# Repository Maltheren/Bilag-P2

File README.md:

# Bilag til P2 projektet ESD210
Alle eksterne bilag til P2 projektet for ESD210 hvor der kan findes følgende mapper:

### Kicad filer
Alle kredsløbsdiagrammer samt PCB designs. Under mappen /PDF kan alle schematics findes i pdf format.

### Kode produkt
De endelige 3 sketches for produktet. Det anbefales at åbne dem via platformIO.
Ellers kan den primære funktionskode findes i /src/main.cpp, samt de udviklede libraries under /lib.
Eksternt brugte libraries i dette projekt er:
- "Arduino.h"
- "RF24.h"

### Tests
Her forefindes de forskellige tests opdelt som enten samlet, Klokke eller MKF

### PC oscilloskop
For at visualisere de samples der tages af arduinoen på MKF-modulet benyttes følgende værktøj
https://x-io.co.uk/serial-oscilloscope/

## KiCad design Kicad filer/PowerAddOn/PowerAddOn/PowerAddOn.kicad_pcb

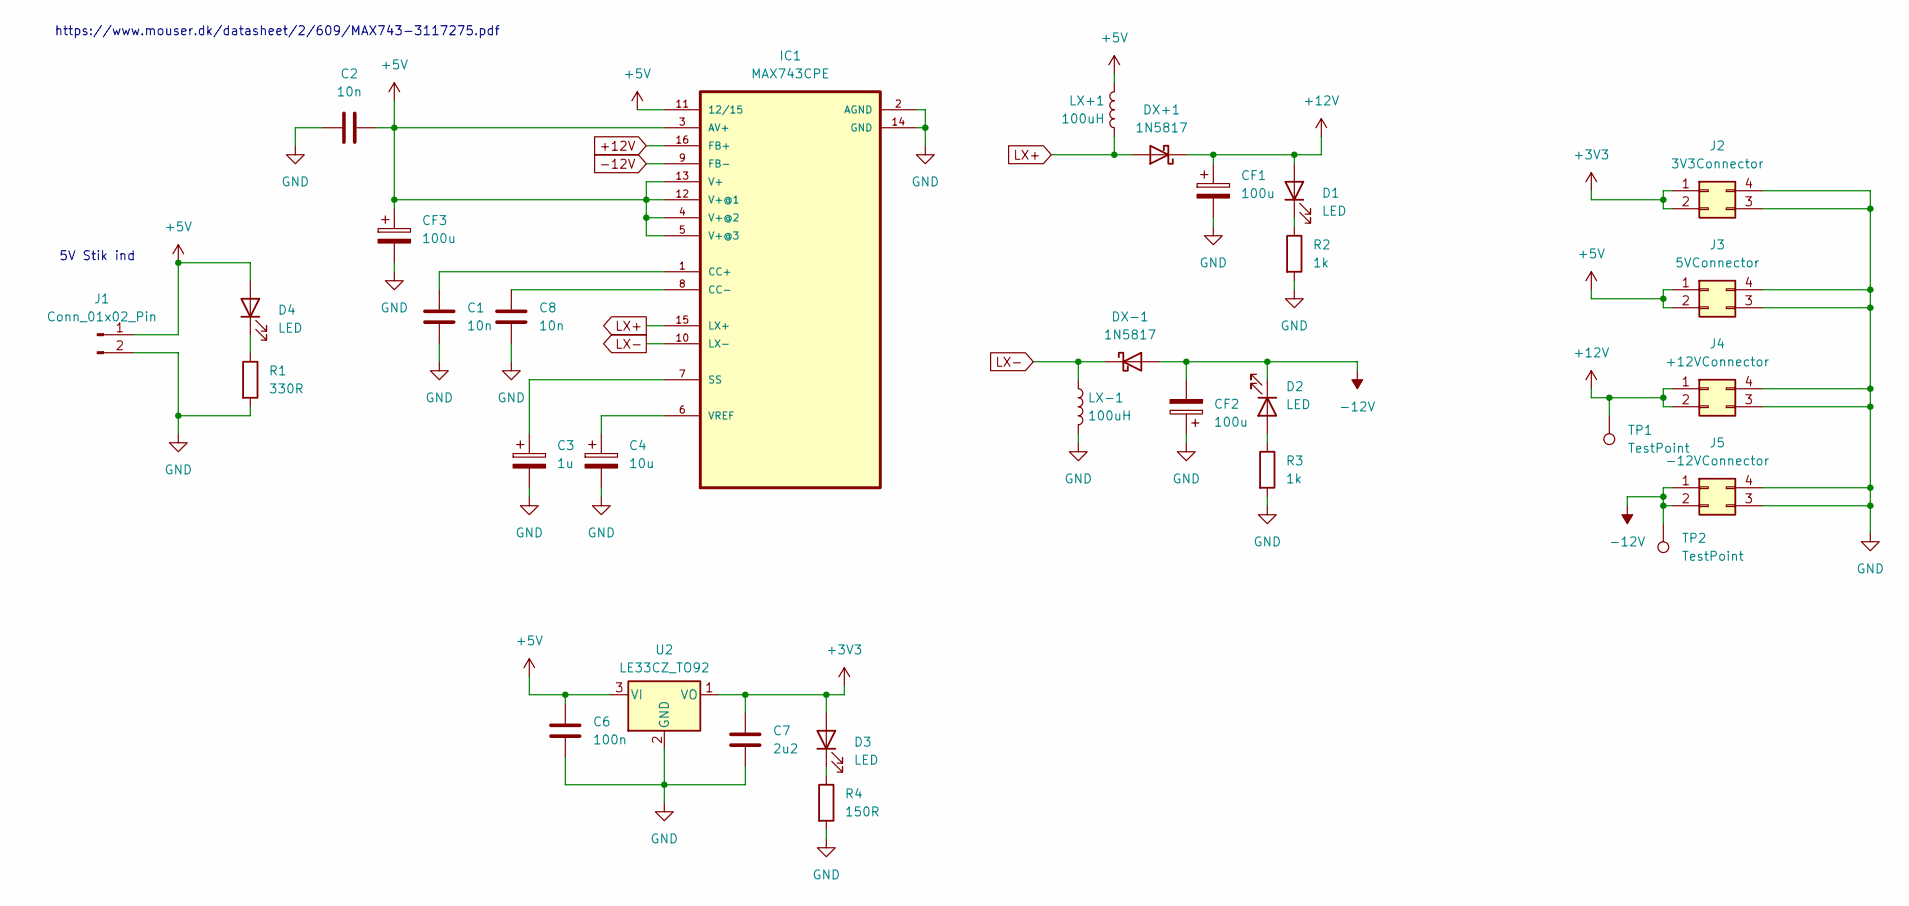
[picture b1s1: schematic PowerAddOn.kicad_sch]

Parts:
C1, C2, C8: 10n; C_Disc_D4.7mm_W2.5mm_P5.00mm
C3: 1u; CP_Radial_D4.0mm_P2.00mm
C4: 10u; CP_Radial_D4.0mm_P2.00mm
C6: 100n; C_0805_2012Metric_Pad1.18x1.45mm_HandSolder
C7: 2u2; C_0805_2012Metric_Pad1.18x1.45mm_HandSolder
CF1, CF2, CF3: 100u; CP_Axial_L10.0mm_D6.0mm_P15.00mm_Horizontal
D1, D2, D3, D4: LED; LED_D3.0mm
DX+1: 1N5817; D_DO-41_SOD81_P10.16mm_Horizontal
DX-1: 1N5817; D_DO-41_SOD81_P10.16mm_Horizontal
IC1: MAX743CPE; DIP794W47P254L1943H457Q16
J1: Conn_01x02_Pin; PinHeader_1x02_P2.54mm_Vertical
J2: 3V3Connector; PinHeader_2x02_P2.54mm_Vertical
J3: 5VConnector; PinHeader_2x02_P2.54mm_Vertical
J4: +12VConnector; PinHeader_2x02_P2.54mm_Vertical
J5: -12VConnector; PinHeader_2x02_P2.54mm_Vertical
LX+1: 100uH; L_Radial_D10.0mm_P5.00mm_Fastron_07P
LX-1: 100uH; L_Radial_D10.0mm_P5.00mm_Fastron_07P
R1: 330R; R_0805_2012Metric_Pad1.20x1.40mm_HandSolder
R2, R3: 1k; R_0805_2012Metric_Pad1.20x1.40mm_HandSolder
R4: 150R; R_0805_2012Metric_Pad1.20x1.40mm_HandSolder
TP1, TP2: TestPoint; TestPoint_Pad_4.0x4.0mm
U2: LE33CZ_TO92; TO-92_Inline

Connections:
+3V3: C7.1, D3.2 (A), J2.1, J2.2, U2.1 (VO)
+5V: C2.2, C6.1, CF3.1, D4.2 (A), IC1.3 (AV+), IC1.4 (V+@2), IC1.5 (V+@3), IC1.11 (12/15), IC1.12 (V+@1), IC1.13 (V+), J1.1, J3.1, J3.2, LX+1.1, U2.3 (VI)
+12V: CF1.1, D1.2 (A), DX+1.1 (K), IC1.16 (FB+), J4.1, J4.2, TP1.1
-12V: CF2.2, D2.1 (K), DX-1.2 (A), IC1.9 (FB-), J5.1, J5.2, TP2.1
GND: C1.2, C2.1, C3.2, C4.2, C6.2, C7.2, C8.2, CF1.2, CF2.1, CF3.2, IC1.2 (AGND), IC1.14 (GND), J1.2, J2.3, J2.4, J3.3, J3.4, J4.3, J4.4, J5.3, J5.4, LX-1.2, R1.2, R2.2, R3.2, R4.2, U2.2 (GND)
LX+: DX+1.2 (A), IC1.15 (LX+), LX+1.2
LX-: DX-1.1 (K), IC1.10 (LX-), LX-1.1
unnamed: D1.1 (K), R2.1
unnamed: D2.2 (A), R3.1
unnamed: D3.1 (K), R4.1
unnamed: D4.1 (K), R1.1
unnamed: C1.1, IC1.1 (CC+)
unnamed: C8.1, IC1.8 (CC-)
unnamed: C3.1, IC1.7 (SS)
unnamed: C4.1, IC1.6 (VREF)

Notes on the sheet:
5V Stik ind
https://www.mouser.dk/datasheet/2/609/MAX743-3117275.pdf

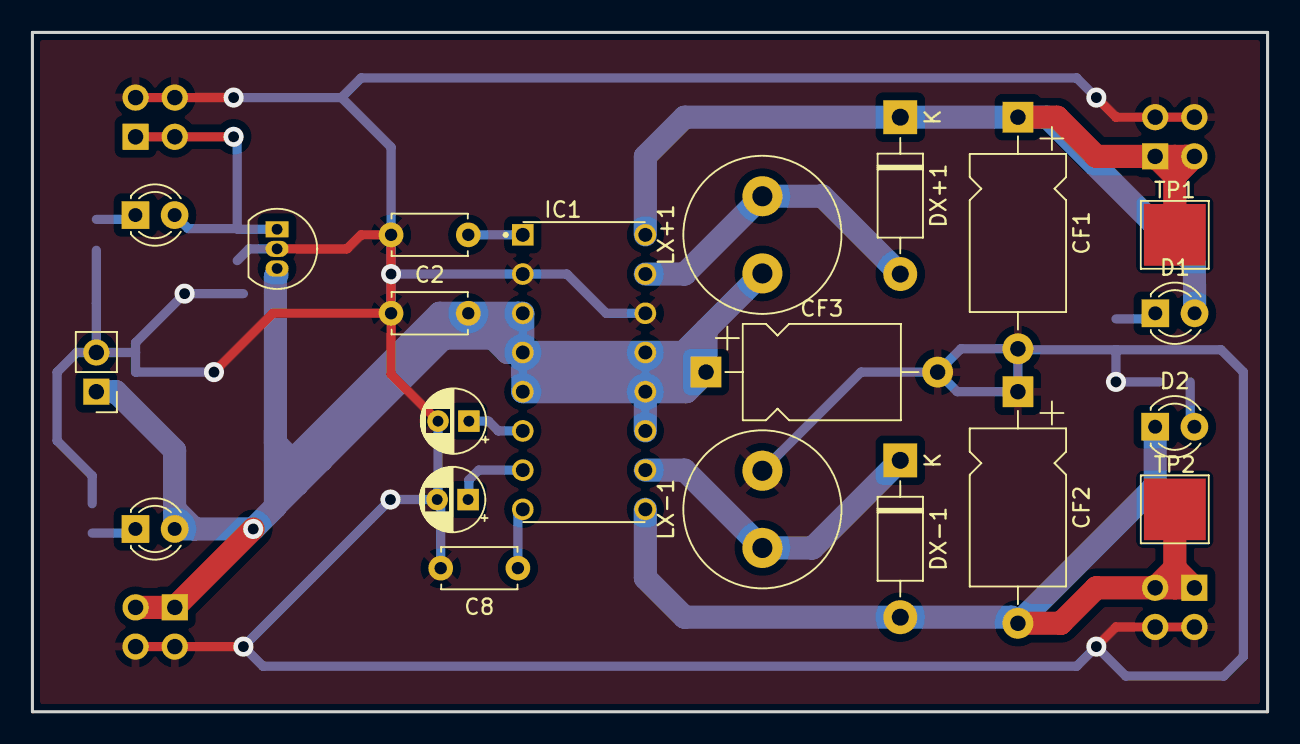
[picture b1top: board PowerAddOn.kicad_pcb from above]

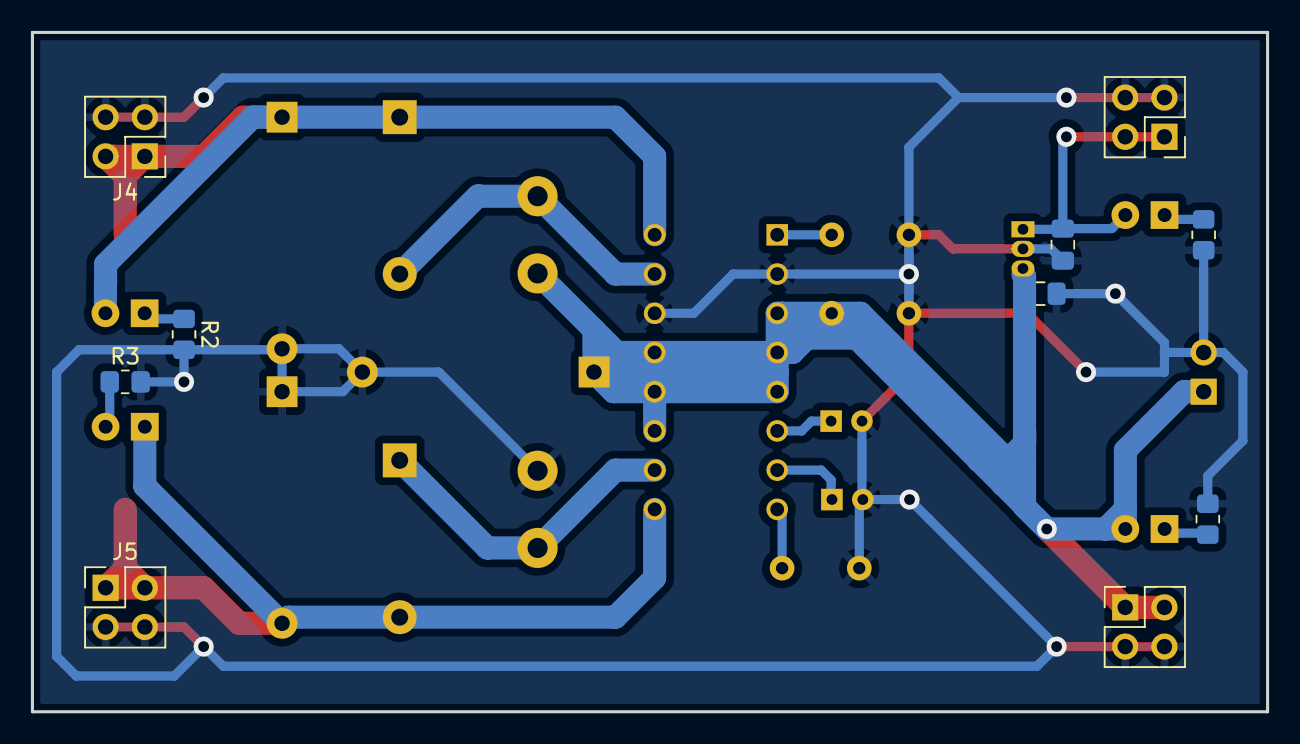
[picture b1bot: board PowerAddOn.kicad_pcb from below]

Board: 2 copper layers, 80.0 x 44.0 mm, 31 parts (10 on the bottom side), 15 nets.

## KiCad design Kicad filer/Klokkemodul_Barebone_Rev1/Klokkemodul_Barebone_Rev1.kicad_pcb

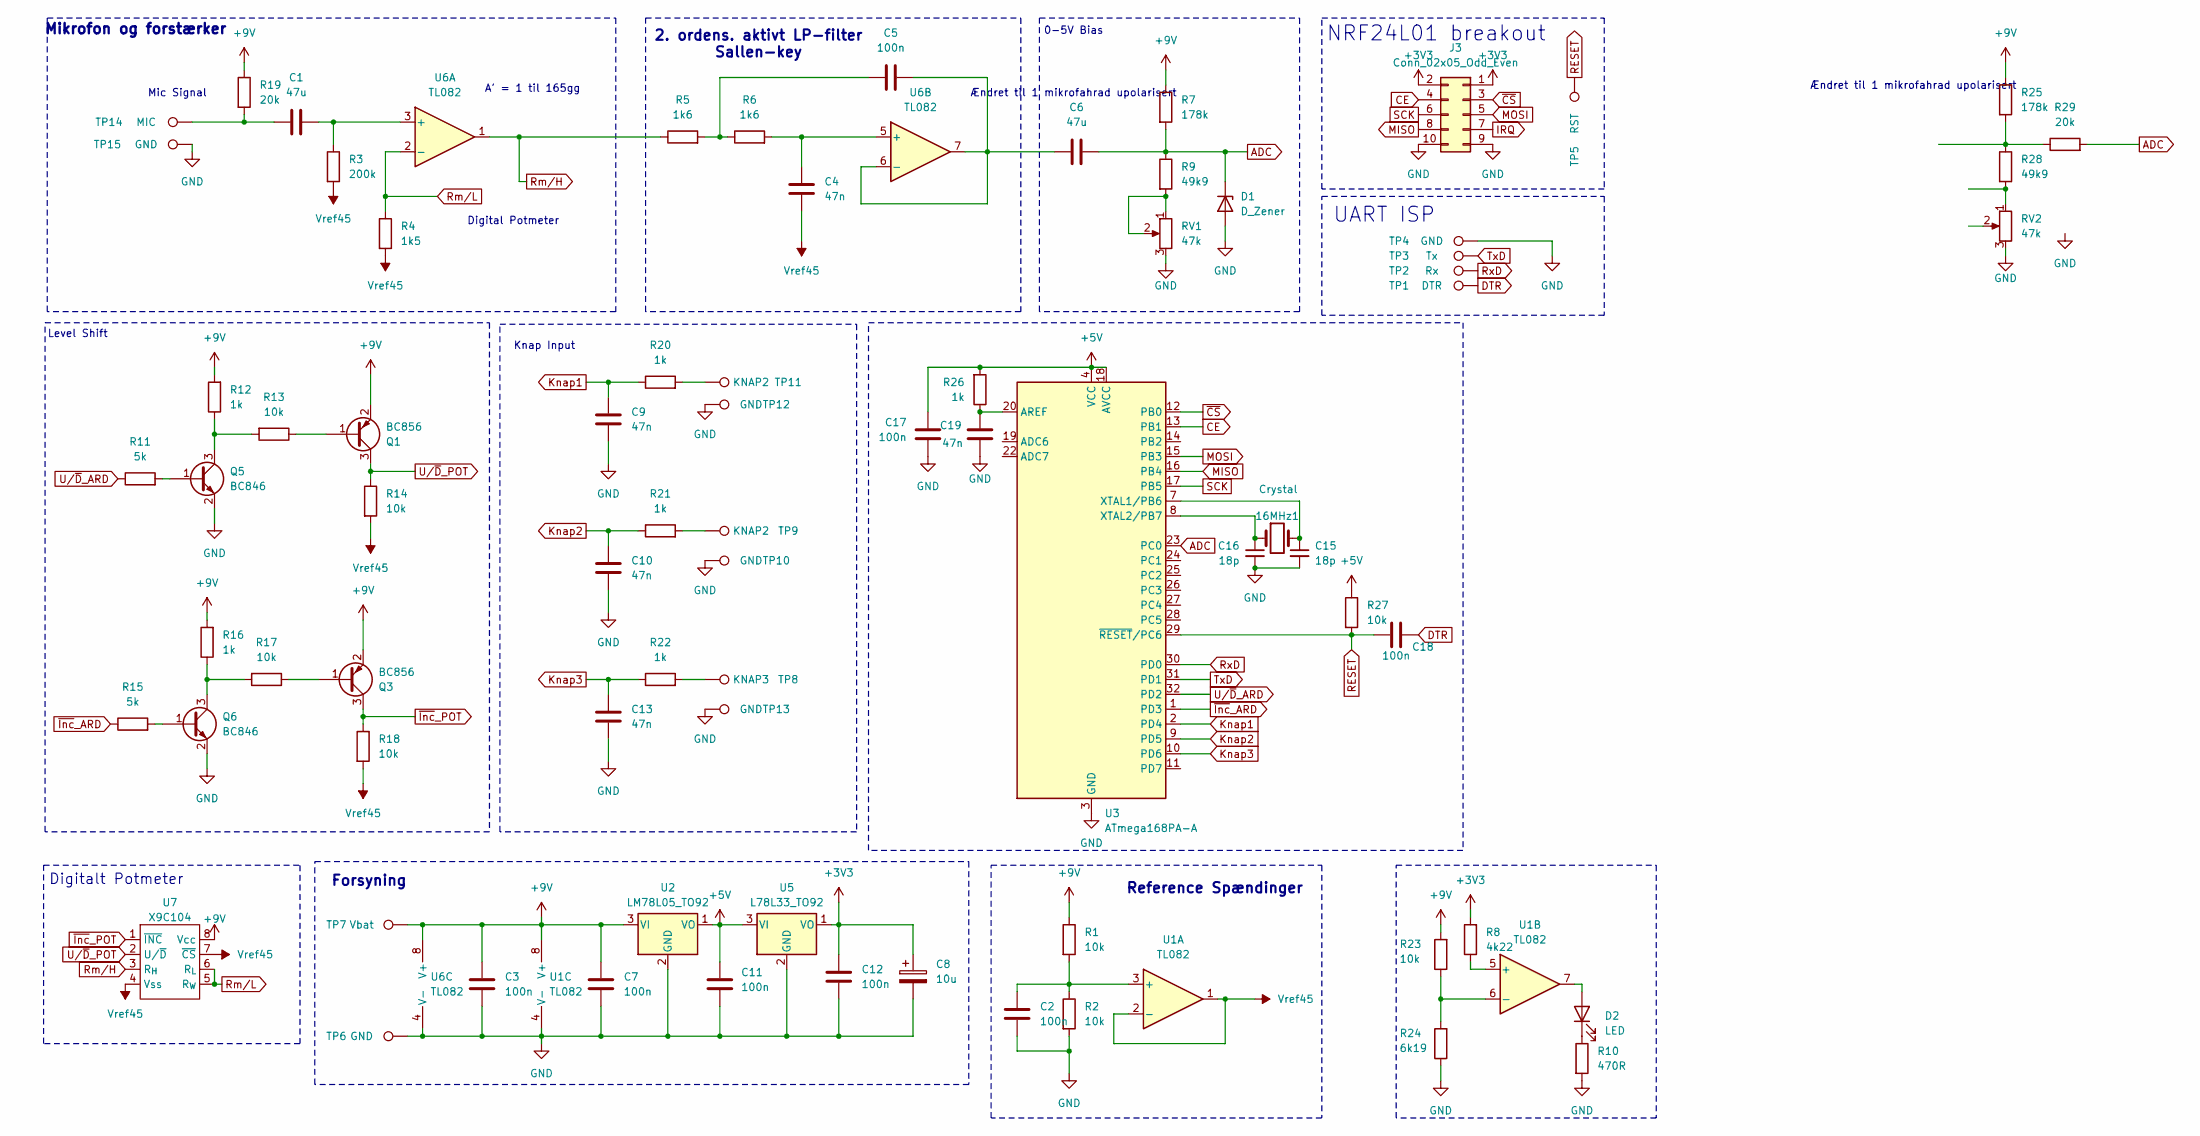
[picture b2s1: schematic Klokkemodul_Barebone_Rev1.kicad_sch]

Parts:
16MHz1: Crystal; Crystal_HC18-U_Vertical
C1, C6: 47u; CP_Radial_D5.0mm_P2.50mm
C2, C3, C5, C7, C11, C12, C17, C18: 100n; C_0603_1608Metric_Pad1.08x0.95mm_HandSolder
C4, C9, C10, C13, C19: 47n; C_0603_1608Metric_Pad1.08x0.95mm_HandSolder
C8: 10u; CP_Radial_D5.0mm_P2.50mm
C15, C16: 18p; C_0603_1608Metric_Pad1.08x0.95mm_HandSolder
D1: D_Zener; D_DO-15_P10.16mm_Horizontal
D2: LED; LED_D3.0mm
J3: Conn_02x05_Odd_Even; PinSocket_2x05_P2.54mm_Vertical
Q1, Q3: BC856; SOT-23
Q5, Q6: BC846; SOT-23
R1, R2, R13, R14, R17, R18, R23, R27: 10k; R_0603_1608Metric_Pad0.98x0.95mm_HandSolder
R3: 200k; R_0603_1608Metric_Pad0.98x0.95mm_HandSolder
R4: 1k5; R_0603_1608Metric_Pad0.98x0.95mm_HandSolder
R5, R6: 1k6; R_0603_1608Metric_Pad0.98x0.95mm_HandSolder
R7, R25: 178k; R_0603_1608Metric_Pad0.98x0.95mm_HandSolder
R8: 4k22; R_0603_1608Metric_Pad0.98x0.95mm_HandSolder
R9, R28: 49k9; R_0603_1608Metric_Pad0.98x0.95mm_HandSolder
R10: 470R; R_0603_1608Metric_Pad0.98x0.95mm_HandSolder
R11, R15: 5k; R_0603_1608Metric_Pad0.98x0.95mm_HandSolder
R12, R16, R20, R21, R22, R26: 1k; R_0603_1608Metric_Pad0.98x0.95mm_HandSolder
R19, R29: 20k; R_0603_1608Metric_Pad0.98x0.95mm_HandSolder
R24: 6k19; R_0603_1608Metric_Pad0.98x0.95mm_HandSolder
RV1, RV2: 47k; Potentiometer_ACP_CA9-V10_Vertical_Hole
TP1: DTR; TestPoint_Pad_2.5x2.5mm
TP2: Rx; TestPoint_Pad_2.5x2.5mm
TP3: Tx; TestPoint_Pad_2.5x2.5mm
TP4, TP6, TP10, TP12, TP13, TP15: GND; TestPoint_Pad_2.5x2.5mm
TP5: RST; TestPoint_Pad_2.5x2.5mm
TP7: Vbat; TestPoint_Pad_2.5x2.5mm
TP8: KNAP3; TestPoint_Pad_2.5x2.5mm
TP9, TP11: KNAP2; TestPoint_Pad_2.5x2.5mm
TP14: MIC; TestPoint_Pad_2.5x2.5mm
U1, U6: TL082; SOIC-8_3.9x4.9mm_P1.27mm
U2: LM78L05_TO92; TO-92_Inline
U3: ATmega168PA-A; TQFP-32_7x7mm_P0.8mm
U5: L78L33_TO92; TO-92_Inline
U7: X9C104; SOIC-8_3.9x4.9mm_P1.27mm

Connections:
+3V3: C8.1, C12.1, J3.1, J3.2, R8.2, U5.1 (VO)
+5V: C11.1, C17.1, R26.2, R27.1, U2.1 (VO), U3.4 (VCC), U3.6 (VCC), U3.18 (AVCC), U5.3 (VI)
+9V: C3.1, C7.1, Q1.2 (E), Q3.2 (E), R1.1, R7.1, R12.2, R16.2, R19.1, R23.2, R25.1, TP7.1, U1.8 (V+), U2.3 (VI), U6.8 (V+), U7.8 (Vcc); also elsewhere on the board
ADC: C6.2, D1.1 (K), R7.2, R9.1, R29.2, U3.23 (PC0)
CE: J3.4, U3.13 (PB1)
DTR: C18.1, TP1.1
GND: C2.2, C3.2, C7.2, C8.2, C9.2, C10.2, C11.2, C12.2, C13.2, C15.2, C16.2, C17.2, C19.2, D1.2 (A), J3.9, J3.10, Q5.2 (E), Q6.2 (E), R2.2, R10.2, R24.1, RV1.3, RV2.3, TP4.1, TP6.1, TP10.1, TP12.1, TP13.1, TP15.1, U1.4 (V-), U2.2 (GND), U3.3 (GND), U3.5 (GND), U3.21 (GND), U5.2 (GND), U6.4 (V-)
IRQ: J3.7
Knap1: C9.1, R20.1, U3.2 (PD4)
Knap2: C10.1, R21.1, U3.9 (PD5)
Knap3: C13.1, R22.1, U3.10 (PD6)
MISO: J3.8, U3.16 (PB4)
MOSI: J3.5, U3.15 (PB3)
unnamed: C1.1, R19.2, TP14.1
unnamed: C5.1, R5.2, R6.1
unnamed: D2.2 (A), U1.7
unnamed: D2.1 (K), R10.1
unnamed 17: Q1.1 (B), R13.1; also elsewhere on the board
unnamed 18: Q3.1 (B), R17.1; also elsewhere on the board
unnamed: Q5.1 (B), R11.2
unnamed: Q5.3 (C), R12.1, R13.2
unnamed: Q6.1 (B), R15.2
unnamed: Q6.3 (C), R16.1, R17.2
unnamed: R9.2, RV1.1, RV1.2
unnamed: R20.2, TP11.1
unnamed: R21.2, TP9.1
unnamed: R22.2, TP8.1
unnamed: R25.2, R28.1, R29.1
unnamed: R28.2, RV2.1
unnamed: C2.1, R1.2, R2.1, U1.3 (+)
unnamed: R8.1, U1.5 (+)
unnamed: R23.1, R24.2, U1.6 (-)
unnamed: C19.1, R26.1, U3.20 (AREF)
unnamed: 16MHz1.2, C15.1, U3.7 (XTAL1/PB6)
unnamed: 16MHz1.1, C16.1, U3.8 (XTAL2/PB7)
unnamed: C1.2, R3.1, U6.3 (+)
unnamed: C4.1, R6.2, U6.5 (+)
unnamed: C5.2, C6.1, U6.6 (-), U6.7
RESET: C18.2, R27.2, TP5.1, U3.29 (~RESET/PC6)
Rm/H: R5.1, U6.1, U7.3 (R_{H})
Rm/L: R4.1, U6.2 (-), U7.5 (R_{W}), U7.6 (R_{L})
RxD: TP2.1, U3.30 (PD0)
SCK: J3.6, U3.17 (PB5)
TxD: TP3.1, U3.31 (PD1)
U/~D_ARD: R11.1, U3.32 (PD2)
U/~D_POT: Q1.3 (C), R14.1, U7.2 (U/~D); also elsewhere on the board
Vref45: C4.2, R3.2, R4.2, R14.2, R18.2, U1.1, U1.2 (-), U7.4 (Vss), U7.7 (~CS)
~CS: J3.3, U3.12 (PB0)
~Inc_ARD: R15.1, U3.1 (PD3)
~Inc_POT: Q3.3 (C), R18.1, U7.1 (~INC); also elsewhere on the board

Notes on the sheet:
Digitalt Potmeter
Digital Potmeter
2. ordens. aktivt LP-filter Sallen-key
A' = 1 til 165gg
0-5V Bias
Ændret til 1 mikrofahrad upolarisert
NRF24L01 breakout
Mic Signal
Knap Input
Forsyning
UART ISP
Level Shift
Reference Spændinger
Mikrofon og forstærker

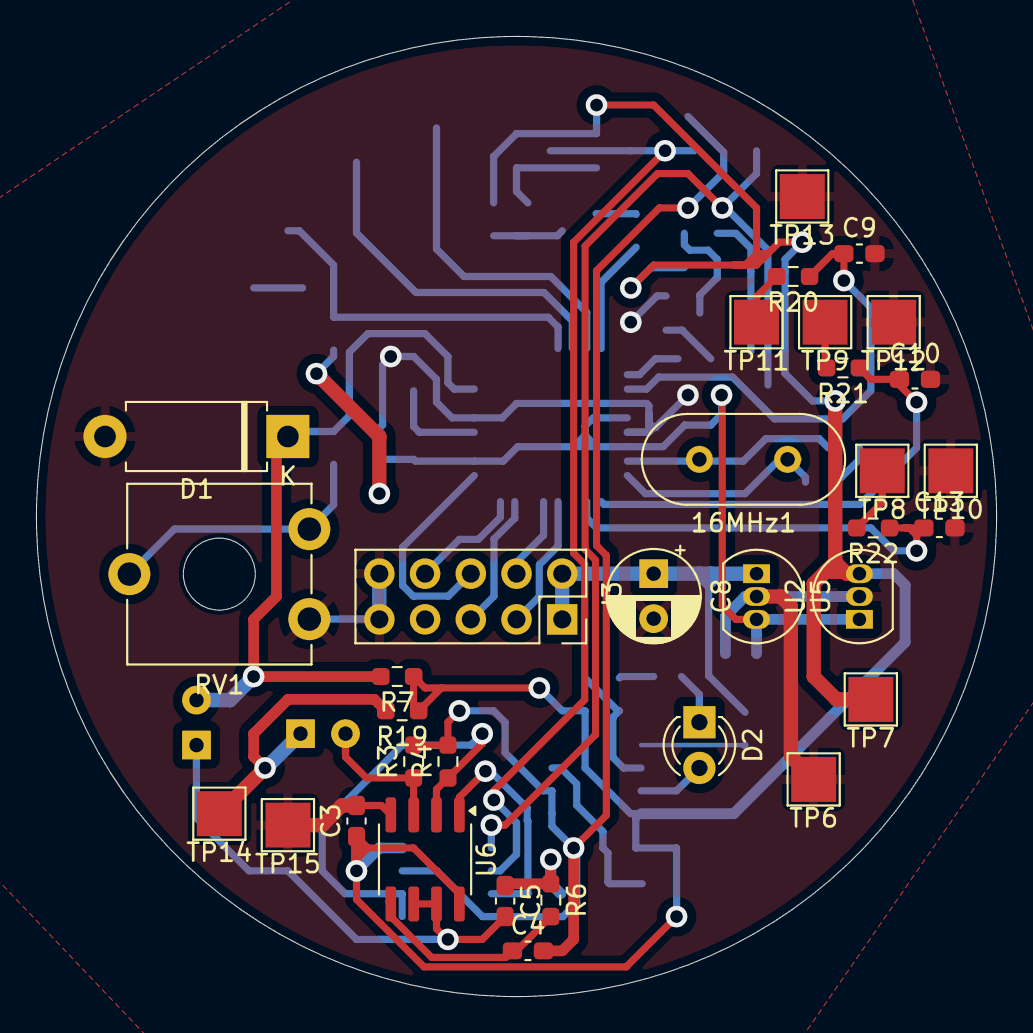
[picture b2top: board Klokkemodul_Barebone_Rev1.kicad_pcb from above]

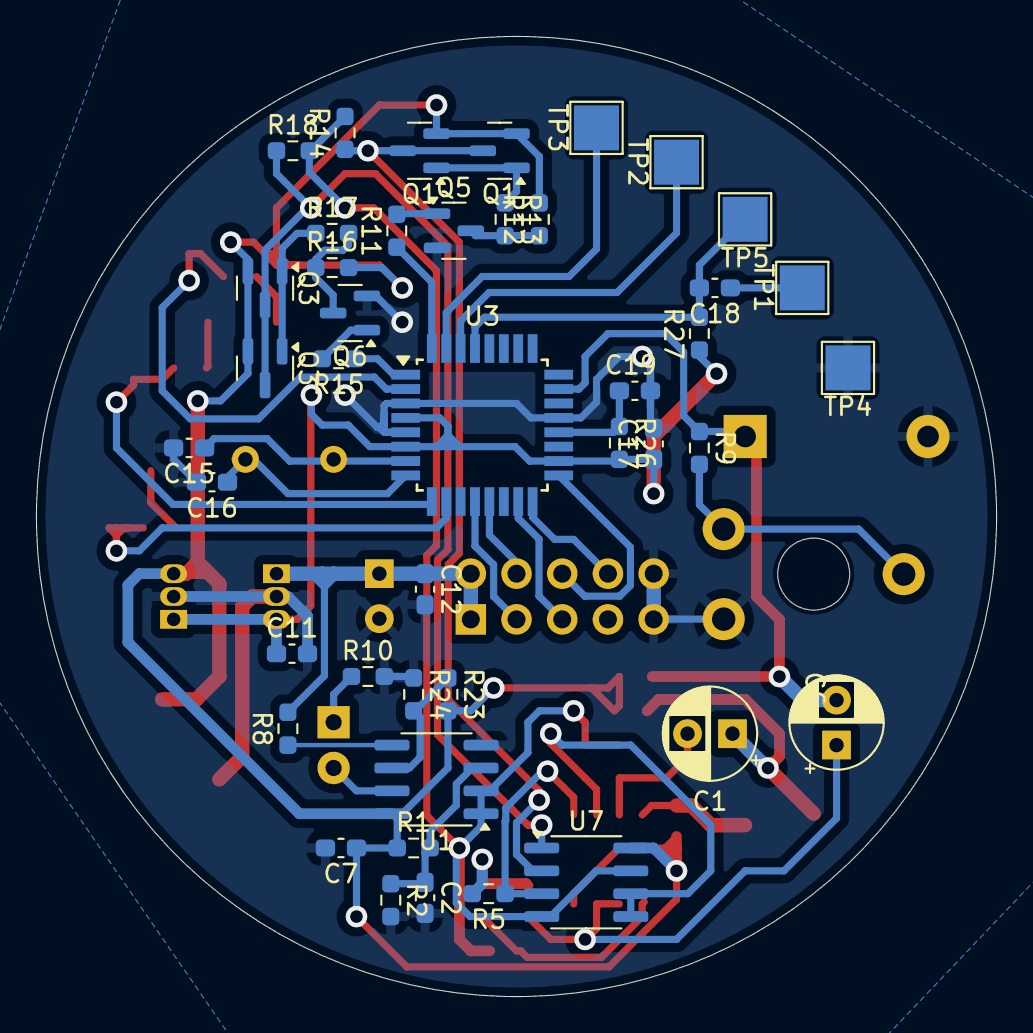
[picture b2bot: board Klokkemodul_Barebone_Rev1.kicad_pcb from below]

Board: 2 copper layers, 53.3 x 53.3 mm, 76 parts (43 on the bottom side), 47 nets.

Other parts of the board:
Q1#2, Q3#2: BC856; SOT-23

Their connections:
+9V: Q1#2.2 (E), Q3#2.2 (E); also elsewhere on the board
unnamed 17: Q1#2.1 (B); also elsewhere on the board
unnamed 18: Q3#2.1 (B); also elsewhere on the board
U/~D_POT: Q1#2.3 (C); also elsewhere on the board
~Inc_POT: Q3#2.3 (C); also elsewhere on the board

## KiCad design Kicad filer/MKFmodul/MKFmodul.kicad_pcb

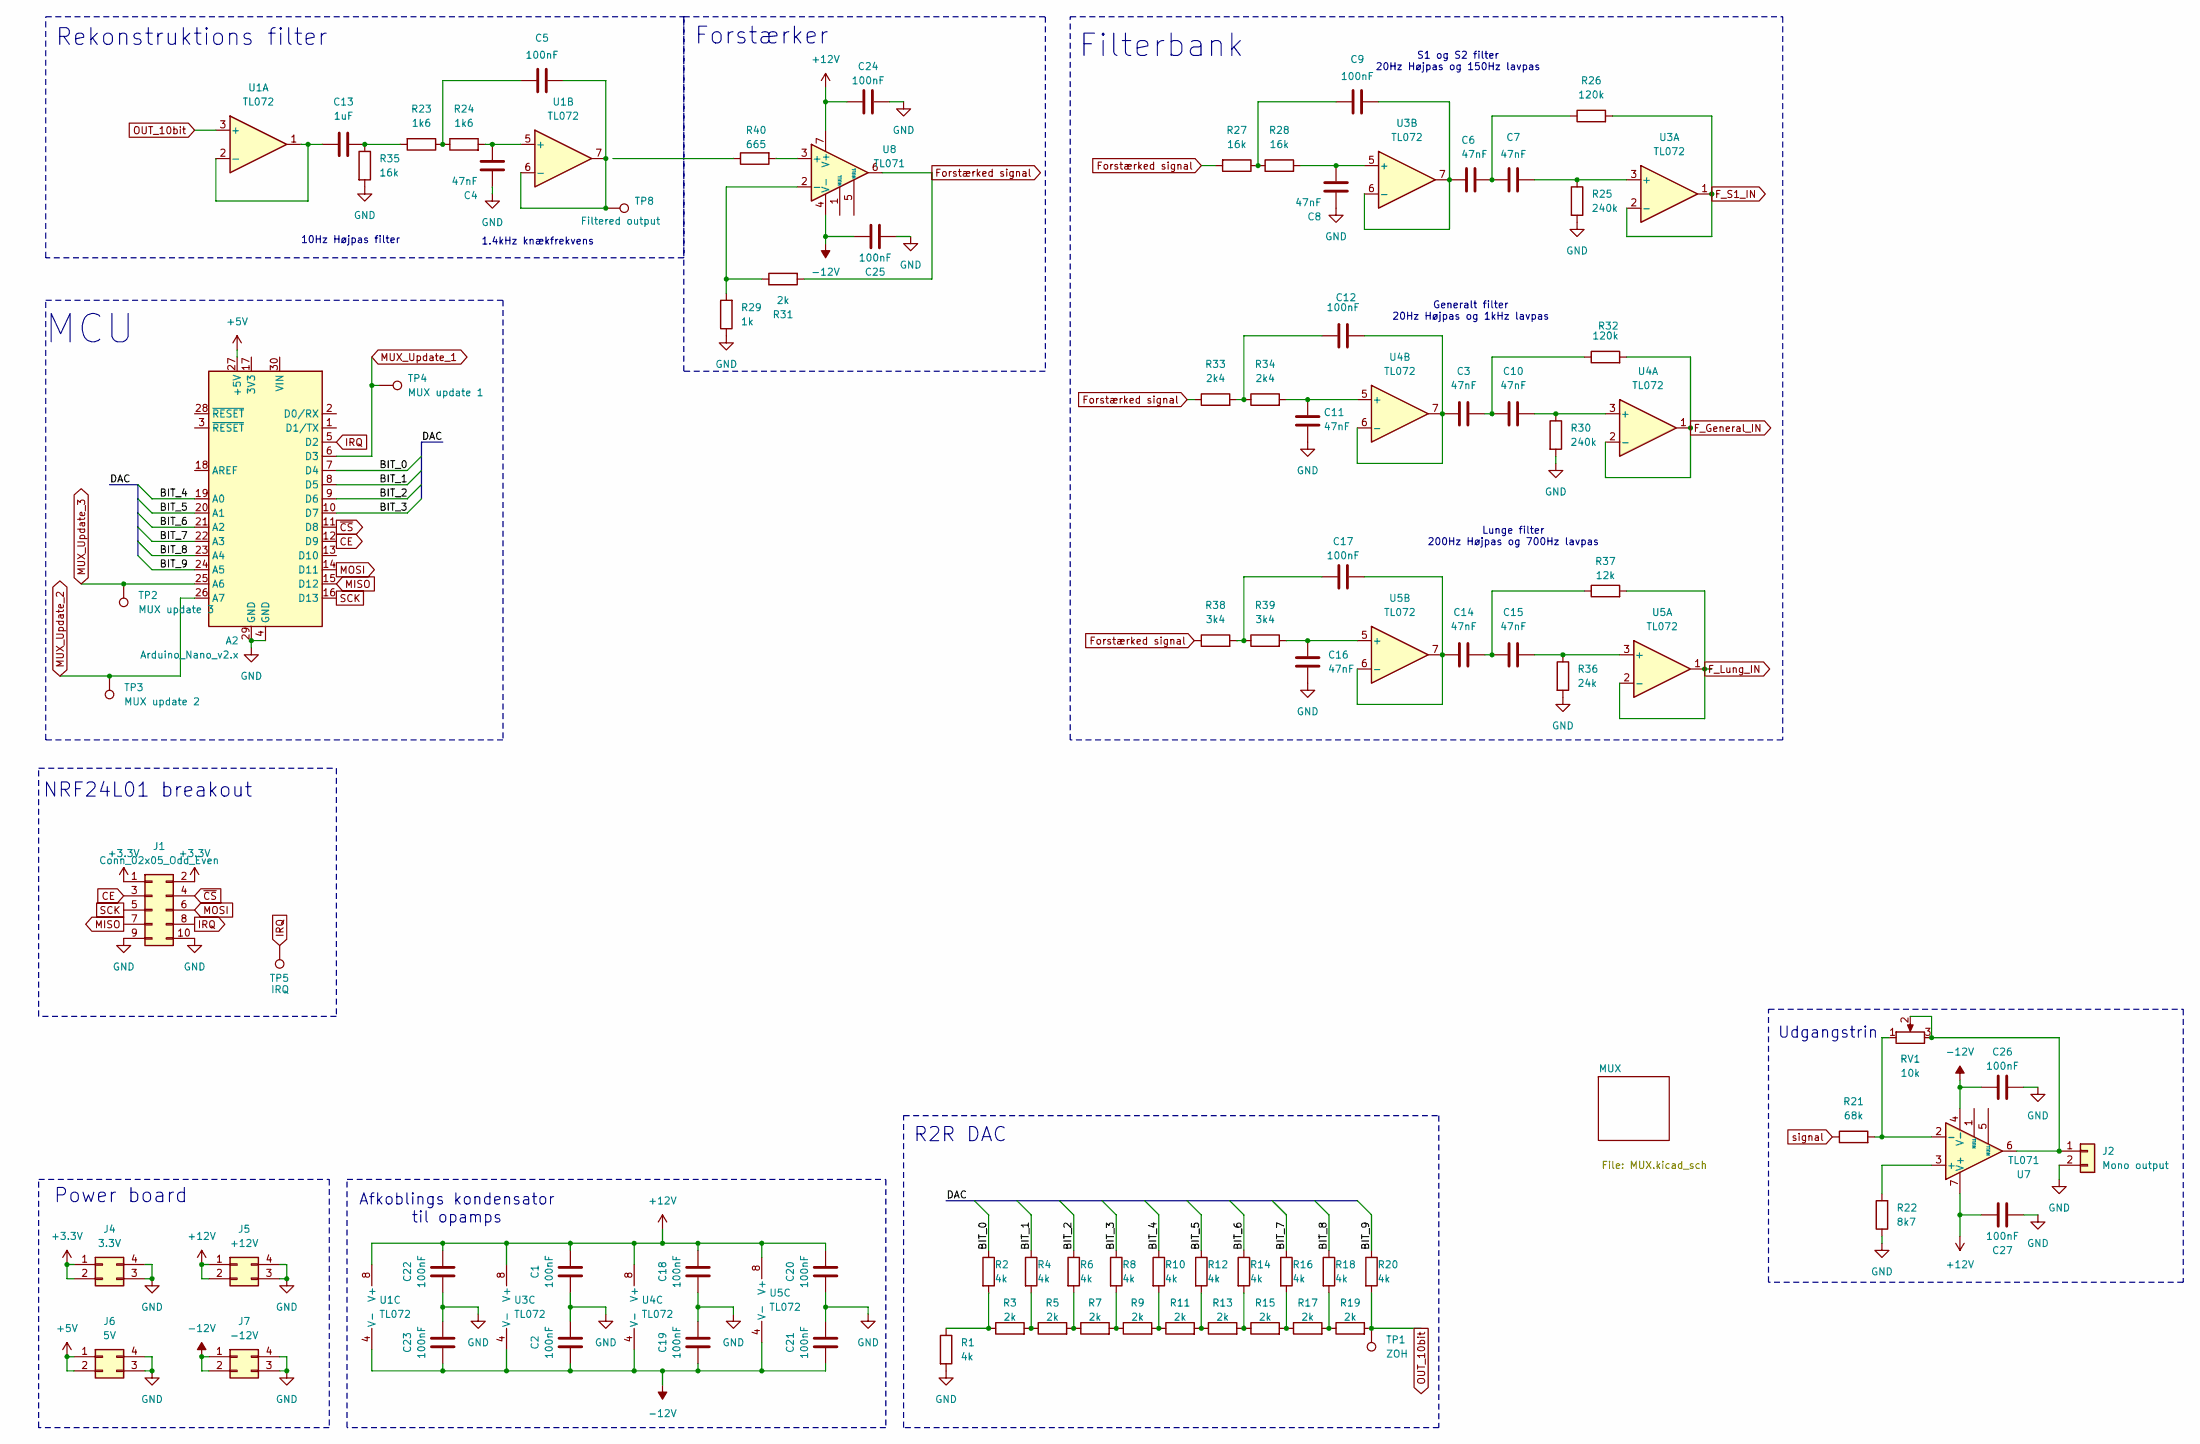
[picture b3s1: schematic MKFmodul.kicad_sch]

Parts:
A2: Arduino_Nano_v2.x; Arduino_Nano
C1, C2, C5, C9, C12, C17, C18, C19, C20, C21, C22, C23, C24, C25, C26, C27: 100nF; C_Disc_D7.0mm_W2.5mm_P5.00mm
C3, C4, C6, C7, C8, C10, C11, C14, C15, C16: 47nF; C_Disc_D7.0mm_W2.5mm_P5.00mm
C13: 1uF; C_Disc_D7.0mm_W2.5mm_P5.00mm
J1: Conn_02x05_Odd_Even; PinSocket_2x05_P2.54mm_Vertical
J2: Mono output; PinHeader_1x02_P2.54mm_Vertical
J4: 3.3V; PinHeader_2x02_P2.54mm_Vertical
J5: +12V; PinHeader_2x02_P2.54mm_Vertical
J6: 5V; PinHeader_2x02_P2.54mm_Vertical
J7: -12V; PinHeader_2x02_P2.54mm_Vertical
R1, R2, R4, R6, R8, R10, R12, R14, R16, R18, R20: 4k; R_Axial_DIN0207_L6.3mm_D2.5mm_P10.16mm_Horizontal
R3, R5, R7, R9, R11, R13, R15, R17, R19, R31: 2k; R_Axial_DIN0207_L6.3mm_D2.5mm_P10.16mm_Horizontal
R21: 68k; R_Axial_DIN0207_L6.3mm_D2.5mm_P10.16mm_Horizontal
R22: 8k7; R_Axial_DIN0207_L6.3mm_D2.5mm_P10.16mm_Horizontal
R23, R24: 1k6; R_Axial_DIN0207_L6.3mm_D2.5mm_P10.16mm_Horizontal
R25, R30: 240k; R_Axial_DIN0207_L6.3mm_D2.5mm_P10.16mm_Horizontal
R26, R32: 120k; R_Axial_DIN0207_L6.3mm_D2.5mm_P10.16mm_Horizontal
R27, R28, R35: 16k; R_Axial_DIN0207_L6.3mm_D2.5mm_P10.16mm_Horizontal
R29: 1k; R_Axial_DIN0207_L6.3mm_D2.5mm_P10.16mm_Horizontal
R33, R34: 2k4; R_Axial_DIN0207_L6.3mm_D2.5mm_P10.16mm_Horizontal
R36: 24k; R_Axial_DIN0207_L6.3mm_D2.5mm_P10.16mm_Horizontal
R37: 12k; R_Axial_DIN0207_L6.3mm_D2.5mm_P10.16mm_Horizontal
R38, R39: 3k4; R_Axial_DIN0207_L6.3mm_D2.5mm_P10.16mm_Horizontal
R40: 665; R_Axial_DIN0207_L6.3mm_D2.5mm_P10.16mm_Horizontal
RV1: 10k; PinHeader_1x03_P2.54mm_Vertical
TP1: ZOH; TestPoint_Pad_3.0x3.0mm
TP2: MUX update 3; TestPoint_Pad_3.0x3.0mm
TP3: MUX update 2; TestPoint_Pad_3.0x3.0mm
TP4: MUX update 1; TestPoint_Pad_3.0x3.0mm
TP5: IRQ; PinHeader_1x01_P2.54mm_Vertical
TP8: Filtered output; PinHeader_1x01_P2.54mm_Vertical
U1, U3, U4, U5: TL072; DIP-8_W7.62mm_LongPads
U7, U8: TL071; DIP-8_W7.62mm_LongPads

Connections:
+3.3V: J1.1, J1.2, J4.1, J4.2
+5V: A2.27 (+5V), J6.1, J6.2; also elsewhere on the board
+12V: C1.2, C18.2, C20.2, C22.2, C24.1, C27.1, J5.1, J5.2, U1.8 (V+), U3.8 (V+), U4.8 (V+), U5.8 (V+), U7.7 (V+), U8.7 (V+); also elsewhere on the board
-12V: C2.1, C19.1, C21.1, C23.1, C25.1, C26.2, J7.1, J7.2, U1.4 (V-), U3.4 (V-), U4.4 (V-), U5.4 (V-), U7.4 (V-), U8.4 (V-); also elsewhere on the board
/BIT_0: A2.7 (D4), R2.1
/BIT_1: A2.8 (D5), R4.1
/BIT_2: A2.9 (D6), R6.1
/BIT_3: A2.10 (D7), R8.1
/BIT_4: A2.19 (A0), R10.1
/BIT_5: A2.20 (A1), R12.1
/BIT_6: A2.21 (A2), R14.1
/BIT_7: A2.22 (A3), R16.1
/BIT_8: A2.23 (A4), R18.1
/BIT_9: A2.24 (A5), R20.1
Amp_signal: R27.2, R31.2, R33.1, R38.1, U8.6
CE: A2.12 (D9), J1.3
F_General_IN: R32.2, U4.1, U4.2 (-); also elsewhere on the board
F_Lung_IN: R37.2, U5.1, U5.2 (-); also elsewhere on the board
F_S1_IN: R26.2, U3.1, U3.2 (-); also elsewhere on the board
GND: A2.4 (GND), A2.29 (GND), C1.1, C2.2, C4.1, C8.1, C11.2, C16.2, C18.1, C19.2, C20.1, C21.2, C22.1, C23.2, C24.2, C25.2, C26.1, C27.2, J1.9, J1.10, J2.2, J4.3, J4.4, J5.3, J5.4, J6.3, J6.4, J7.3, J7.4, R1.2, R22.1, R25.2, R29.1, R30.2, R35.2, R36.2; also elsewhere on the board
IRQ: A2.5 (D2), J1.8, TP5.1
MISO: A2.15 (D12), J1.7
MOSI: A2.14 (D11), J1.6
MUX_Update_1: A2.6 (D3), TP4.1; also elsewhere on the board
MUX_Update_2: A2.26 (A7), TP3.1; also elsewhere on the board
MUX_Update_3: A2.25 (A6), TP2.1; also elsewhere on the board
unnamed: C5.1, R23.1, R24.1
unnamed: C6.1, C7.2, R26.1
unnamed: C9.1, R27.1, R28.1
unnamed: C3.2, C10.1, R32.1
unnamed: C12.1, R33.2, R34.1
unnamed: C13.2, R23.2, R35.1
unnamed: C14.2, C15.1, R37.1
unnamed: C17.1, R38.2, R39.1
unnamed: J2.1, RV1.2, RV1.3, U7.6
unnamed: R1.1, R2.2, R3.1
unnamed: R3.2, R4.2, R5.1
unnamed: R5.2, R6.2, R7.1
unnamed: R7.2, R8.2, R9.1
unnamed: R9.2, R10.2, R11.1
unnamed: R11.2, R12.2, R13.1
unnamed: R13.2, R14.2, R15.1
unnamed: R15.2, R16.2, R17.1
unnamed: R17.2, R18.2, R19.1
unnamed: C13.1, U1.1, U1.2 (-)
unnamed: C4.2, R24.2, U1.5 (+)
unnamed: C5.2, TP8.1, U1.6 (-), U1.7
unnamed: C7.1, R25.1, U3.3 (+)
unnamed: C8.2, R28.2, U3.5 (+)
unnamed: C6.2, C9.2, U3.6 (-), U3.7
unnamed: C10.2, R30.1, U4.3 (+)
unnamed: C11.1, R34.2, U4.5 (+)
unnamed: C3.1, C12.2, U4.6 (-), U4.7
unnamed: C15.2, R36.1, U5.3 (+)
unnamed: C16.1, R39.2, U5.5 (+)
unnamed: C14.1, C17.2, U5.6 (-), U5.7
unnamed: R22.2, U7.3 (+)
unnamed: R21.2, RV1.1, U7.2 (-)
unnamed: R40.2, U8.3 (+)
unnamed: R29.2, R31.1, U8.2 (-)
OUT_10bit: R19.2, R20.2, TP1.1, U1.3 (+)
SCK: A2.16 (D13), J1.5
signal: R21.1; also elsewhere on the board
~CS: A2.11 (D8), J1.4

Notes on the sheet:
1.4kHz knækfrekvens
S1 og S2 filter 20Hz Højpas og 150Hz lavpas
MCU
10Hz Højpas filter
Forstærker
Rekonstruktions filter
Power board
Generalt filter 20Hz Højpas og 1kHz lavpas
R2R DAC
NRF24L01 breakout
Lunge filter 200Hz Højpas og 700Hz lavpas
Udgangstrin
Filterbank
Afkoblings kondensator til opamps

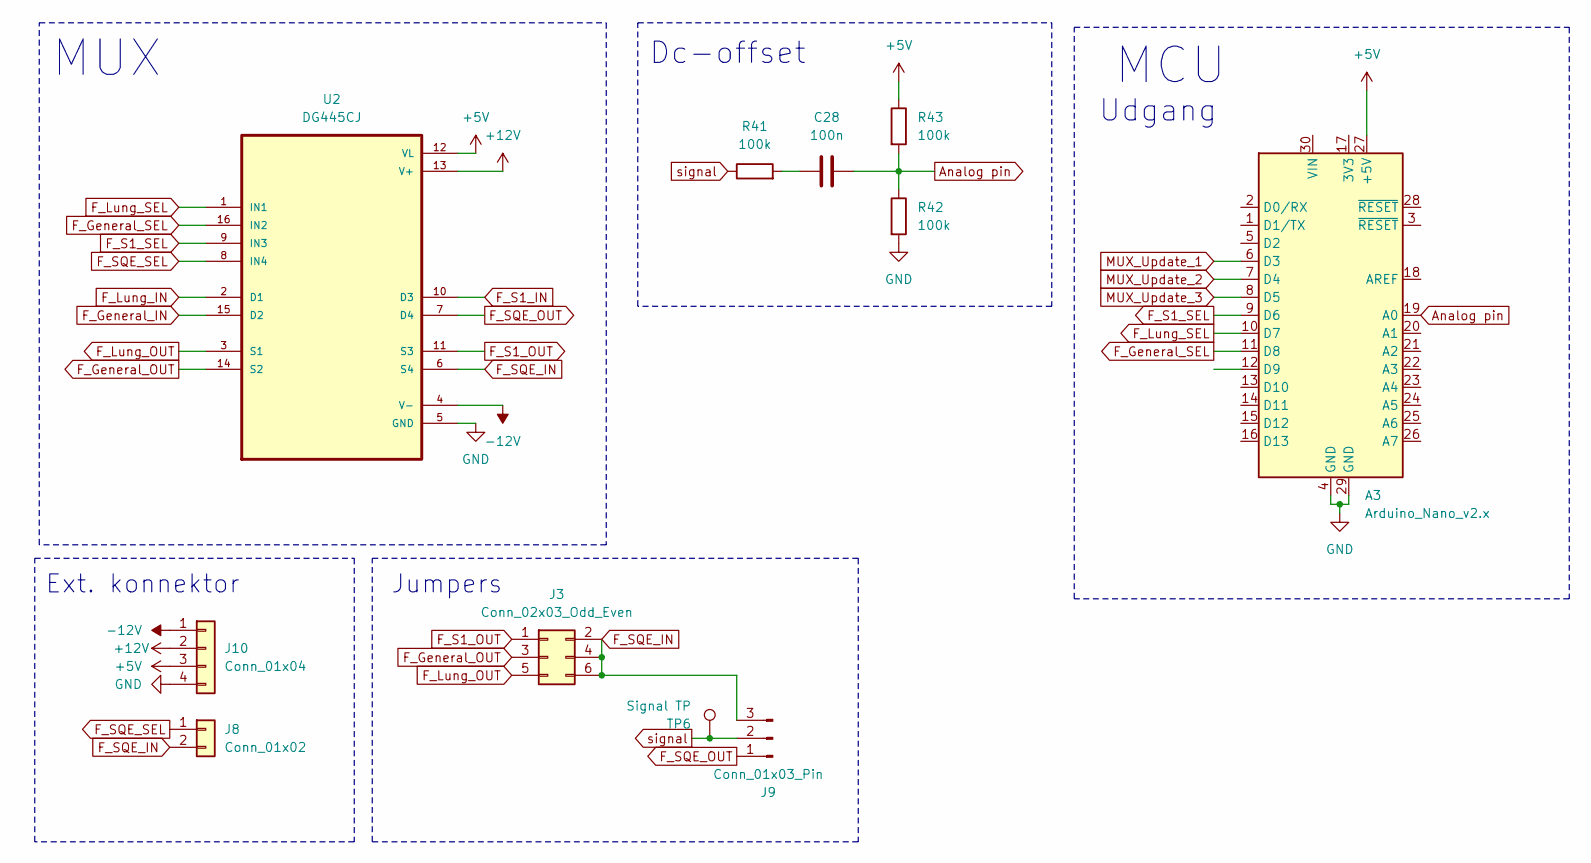
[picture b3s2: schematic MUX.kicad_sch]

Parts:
A3: Arduino_Nano_v2.x; Arduino_Nano
C28: 100n; C_Disc_D7.0mm_W2.5mm_P5.00mm
J3: Conn_02x03_Odd_Even; PinHeader_2x03_P2.54mm_Vertical
J8: Conn_01x02; PinHeader_1x02_P2.54mm_Vertical
J9: Conn_01x03_Pin; PinHeader_1x03_P2.54mm_Vertical
J10: Conn_01x04; PinHeader_1x04_P2.54mm_Vertical
R41, R42, R43: 100k; R_Axial_DIN0207_L6.3mm_D2.5mm_P10.16mm_Horizontal
TP6: Signal TP; PinHeader_1x01_P2.54mm_Vertical
U2: DG445CJ; DIP794W47P254L1943H457Q16

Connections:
+5V: A3.27 (+5V), J10.3, R43.1, U2.12 (VL); also elsewhere on the board
+12V: J10.2, U2.13 (V+); also elsewhere on the board
-12V: J10.1, U2.4 (V-); also elsewhere on the board
Analog pin: A3.19 (A0), C28.2, R42.1, R43.2
F_General_IN: U2.15 (D2); also elsewhere on the board
F_General_OUT: J3.3, U2.14 (S2)
F_General_SEL: A3.11 (D8), U2.16 (IN2)
F_Lung_IN: U2.2 (D1); also elsewhere on the board
F_Lung_OUT: J3.5, U2.3 (S1)
F_Lung_SEL: A3.10 (D7), U2.1 (IN1)
F_S1_IN: U2.10 (D3); also elsewhere on the board
F_S1_OUT: J3.1, U2.11 (S3)
F_S1_SEL: A3.9 (D6), U2.9 (IN3)
F_SQE_IN: J3.2, J3.4, J3.6, J8.2, J9.3, U2.6 (S4)
F_SQE_OUT: J9.1, U2.7 (D4)
F_SQE_SEL: J8.1, U2.8 (IN4)
GND: A3.4 (GND), A3.29 (GND), J10.4, R42.2, U2.5 (GND); also elsewhere on the board
MUX_Update_1: A3.6 (D3); also elsewhere on the board
MUX_Update_2: A3.7 (D4); also elsewhere on the board
MUX_Update_3: A3.8 (D5); also elsewhere on the board
unnamed: C28.1, R41.2
signal: J9.2, R41.1, TP6.1; also elsewhere on the board

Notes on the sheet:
Jumpers
MUX
Udgang
Dc-offset
Ext. konnektor
MCU

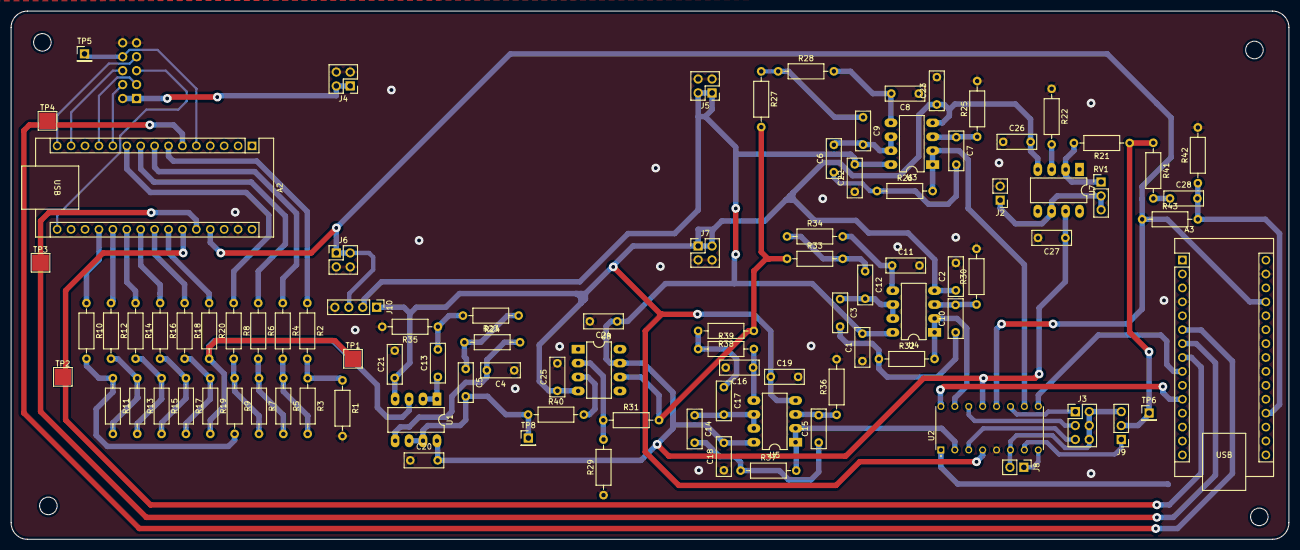
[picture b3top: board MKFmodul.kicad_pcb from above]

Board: 2 copper layers, 233.2 x 96.4 mm, 98 parts (1 on the bottom side), 75 nets.
